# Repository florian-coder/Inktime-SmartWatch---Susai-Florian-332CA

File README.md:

# InkTime v6 — E-Paper Smartwatch

## Overview

InkTime is an e-paper smartwatch built around the **nRF52840** microcontroller, featuring a 1.54" e-paper display, Bluetooth Low Energy connectivity, haptic feedback, and an accelerometer. The watch is powered by a 250mAh LiPo battery managed by a dedicated charger IC with USB-C charging support.

---

## Block Diagram

```
                                    ┌──────────────┐
                                    │   USB-C (J4)  │
                                    │ KH-TYPE-C-16P │
                                    └──────┬───────┘
                                           │ VBUS, D+, D-
                                    ┌──────▼───────┐
                                    │  ESD Protect  │
                                    │ USBLC6-2SC6Y  │
                                    │     (D4)      │
                                    └──────┬───────┘
                              D+,D- │      │ VBUS
                         ┌──────────┘      │
                         │          ┌──────▼───────┐
                         │          │ LiPo Charger  │
                         │          │  BQ25180 (IC3)│
                         │          └──────┬───────┘
                         │                 │ VBAT
                         │          ┌──────▼───────┐
                         │          │  DC/DC Conv   │
                         │          │ RT6160 (IC2)  │
                         │          └──────┬───────┘
                         │                 │ 3V3 (VREG)
                         │                 │
                  ┌──────▼─────────────────▼──────────┐
                  │                                    │
                  │         nRF52840 (U$1)             │
                  │                                    │
                  │  SPI: MOSI, SCK, CS, DC, RST, BUSY │
                  │  I2C: SDA, SCL                     │
                  │  GPIO: Buttons, Haptic EN           │
                  │  USB: D+, D-                       │
                  │  RF: ANT                           │
                  │  SWD: SWDIO, SWDCLK                │
                  │                                    │
                  └─┬──────┬──────┬──────┬──────┬──┬──┘
                    │      │      │      │      │  │
              ┌─────▼──┐ ┌─▼────┐│ ┌────▼─┐ ┌──▼┐ │
              │E-Paper ││ │ IMU  ││ │Haptic│ │ANT│ │
              │Display ││ │BMA423││ │Driver│ │   │ │
              │  (J1)  ││ │(IC1) ││ │DRV   │ │2.4│ │
              │503480  ││ │      ││ │2605  │ │GHz│ │
              └────────┘│ └──────┘│ │(IC4) │ └───┘ │
                        │        │ └──────┘        │
                   ┌────▼───┐ ┌──▼─────┐    ┌─────▼──┐
                   │  Fuel   │ │Buttons │    │  SWD   │
                   │ Gauge   │ │SW1-SW3 │    │  J2    │
                   │MAX17048 │ │        │    │TC2030  │
                   │  (U1)   │ │        │    │        │
                   └─────────┘ └────────┘    └────────┘
```

### Communication Interfaces

| Interface | Components | Signals |
|-----------|-----------|---------|
| SPI | E-Paper Display (J1) | MOSI, SCK, EPD_CS, EPD_DC, EPD_RST, EPD_BUSY |
| I2C | IC1 (IMU), IC2 (DC/DC), IC3 (Charger), IC4 (Haptic), U1 (Fuel Gauge) | SDA, SCL (pull-ups R13=3K3, R14=3K3) |
| USB 2.0 | USB-C Connector (J4) via ESD (D4) | D+, D- (differential 90Ω) |
| SWD | Tag-Connect (J2) | SWDIO, SWDCLK, SWO, RESET |
| GPIO | Buttons (SW1-SW3), Haptic enable, Interrupts | Various P0.xx/P1.xx pins |
| RF | Chip Antenna (ANT1) via matching network | 50Ω controlled impedance trace |

---

## Bill of Materials (BOM)

### Main ICs

| Ref | Component | Package | Value/Description | Qty | Datasheet | Source |
|-----|-----------|---------|-------------------|-----|-----------|--------|
| U$1 | nRF52840-QIAA | QFN-73 7x7mm | BLE SoC, ARM Cortex-M4F, 1MB Flash | 1 | [Datasheet](https://infocenter.nordicsemi.com/pdf/nRF52840_PS_v1.1.pdf) | [JLCPCB](https://jlcpcb.com/partdetail/Nordic_Semiconductor-nRF52840_QIAA_R7/C190794) |
| IC1 | BMA423 | LGA-12 2x2mm | 3-axis accelerometer (IMU) | 1 | [Datasheet](https://www.bosch-sensortec.com/products/motion-sensors/accelerometers/bma423/) | [TME](https://www.tme.eu/en/details/bma423/accelerometers/) |
| IC2 | RT6160AWSC | WLCSP-20 | DC/DC Buck-Boost converter | 1 | [Datasheet](https://www.richtek.com/assets/product_file/RT6160A/DS6160A-05.pdf) | [JLCPCB](https://jlcpcb.com/partdetail/Richtek-RT6160AWSC/C2828074) |
| IC3 | BQ25180YBGR | DSBGA-15 | LiPo Battery Charger | 1 | [Datasheet](https://www.ti.com/lit/ds/symlink/bq25180.pdf) | [JLCPCB](https://jlcpcb.com/partdetail/Texas_Instruments-BQ25180YBGR/C2682568) |
| IC4 | DRV2605YZFR | DSBGA-12 | Haptic Driver | 1 | [Datasheet](https://www.ti.com/lit/ds/symlink/drv2605.pdf) | [JLCPCB](https://jlcpcb.com/partdetail/Texas_Instruments-DRV2605YZFR/C527428) |
| U1 | MAX17048G+T10 | TDFN-8 | Fuel Gauge (battery level) | 1 | [Datasheet](https://datasheets.maximintegrated.com/en/ds/MAX17048-MAX17049.pdf) | [JLCPCB](https://jlcpcb.com/partdetail/Analog_Devices-MAX17048G_T10/C2682568) |

### Connectors & Electromechanical

| Ref | Component | Description | Qty | Source |
|-----|-----------|-------------|-----|--------|
| J1 | 503480-2400 (Molex) | 24-pin FPC connector for e-paper | 1 | [TME](https://www.tme.eu/en/details/503480-2400/ffc-fpc-connectors/) |
| J2 | TC2030-IDC | 6-pin Tag-Connect SWD programmer | 1 | [TME](https://www.tme.eu/en/details/tc2030-idc/) |
| J4 | KH-TYPE-C-16P | USB Type-C 16-pin connector | 1 | [JLCPCB](https://jlcpcb.com/partdetail/Kinghelm-KH_TYPE_C_16P/C2765186) |
| SW1-SW3 | EVP-AKE31A (Panasonic) | Tactile switch 3x2.5mm | 3 | [TME](https://www.tme.eu/en/details/evp-ake31a/micro-switches/) |
| ANT1 | 2450AT18B100E | 2.4GHz chip antenna | 1 | [TME](https://www.tme.eu/en/details/2450at18b100e/) |

### Passive Components — Crystals

| Ref | Value | Description | Qty |
|-----|-------|-------------|-----|
| X1 | 32MHz | Main crystal for nRF52840 | 1 |
| X2 | 32.768kHz | RTC crystal for low-power timekeeping | 1 |

### Passive Components — Inductors

| Ref | Value | Description | Qty |
|-----|-------|-------------|-----|
| L1 | 47µH (FTC252012SR47MBCA) | DC/DC main inductor | 1 |
| L3 | 3.9nH | RF matching network | 1 |
| L5 | 68µH | E-paper drive inductor | 1 |
| U$2, U$4, U$5 | 10µH | MCU inductors (DCC/DCCH) | 3 |

### Passive Components — Capacitors

| Ref | Value | Description | Qty |
|-----|-------|-------------|-----|
| C1, C17, C18 | 12pF | Crystal load capacitors | 3 |
| C3, C4 | 1pF | RF matching | 2 |
| C5, C6, C7, C19, C22 | 100nF | Bypass/decoupling MCU & IMU | 5 |
| C8 | 100pF | DEC4 bypass | 1 |
| C9 | 820pF | RF matching | 1 |
| C11, C14, C20, C21 | 4.7µF | Bulk decoupling MCU | 4 |
| C15 | 1.0µF | VDDH capacitor | 1 |
| C16 | 47nF | DEC4 capacitor | 1 |
| C23, C2, C30 | 0.1µF | Bypass DC/DC, Haptic, USB | 3 |
| C24 | 10µF | DC/DC output | 1 |
| C25, C33 | 22µF | DC/DC input/output | 2 |
| C27, C28, C29 | 1µF | Button debounce | 3 |
| C31 | 4.7µF | USB bulk capacitor | 1 |
| C32-C44 | 1µF/50V | E-paper drive capacitors | 9 |
| C37, C38, C4 | 1µF | Charger & haptic bypass | 3 |
| C39 | 10µF | Charger output | 1 |
| C1-EP-DR | 4.7µF/25V | E-paper drive main cap | 1 |
| C10, C12, C13 | N.C. | Not connected (reserved) | 3 |

### Passive Components — Resistors

| Ref | Value | Description | Qty |
|-----|-------|-------------|-----|
| R1, R2, R3 | 0Ω | IMU configuration jumpers | 3 |
| R6, R7, R8 | 10K | Button pull-up resistors | 3 |
| R9, R12, R15 | 10K | Charger TS, E-paper config | 3 |
| R10 | 0.47Ω | E-paper current sense | 1 |
| R11 | 2.2Ω | E-paper type select | 1 |
| R13, R14 | 3K3 | I2C pull-ups (SCL, SDA) | 2 |
| R16 | 5K1 | USB-C CC resistor | 1 |

### Semiconductors

| Ref | Component | Description | Qty |
|-----|-----------|-------------|-----|
| D1, D2, D3 | MBR0530 | Schottky diodes (e-paper drive) | 3 |
| D4 | USBLC6-2SC6Y | USB ESD protection | 1 |
| Q1 | SI1308EDL-T1-GE3 | N-MOSFET (e-paper drive) | 1 |
| U$3 | DMG2305UX-7 | P-MOSFET (e-paper drive) | 1 |

### Off-Board Components

| Component | Model | Dimensions | Description |
|-----------|-------|------------|-------------|
| Battery | LP502030 (Akyga AKY0106) | 30×20×5mm | 3.7V 250mAh LiPo |
| Display | WSH-12561 (Waveshare) | 31.8×37.32×1.05mm | 1.54" e-paper 200x200px |
| Shaker | FIT0774 (DFRobot) | Ø10×2.7mm | Mini vibration motor |

---

## Pin Assignment — nRF52840 (U$1)

### SPI — E-Paper Display

| nRF52840 Pin | Signal | Direction | Connected To | Purpose |
|-------------|--------|-----------|-------------|---------|
| P0.13 | MOSI | Output | J1 pin 14 | SPI data to display |
| P0.14 | SCK | Output | J1 pin 13 | SPI clock |
| P1.01 | EPD_CS | Output | J1 pin 12 | Chip select (active low) |
| P1.02 | EPD_DC | Output | J1 pin 11 | Data/Command select |
| P0.15 | EPD_RST | Output | J1 pin 10 | Display reset |
| P0.16 | EPD_BUSY | Input | J1 pin 9 | Display busy status |

**Why these pins:** P0.13 and P0.14 are the default SPI MOSI/SCK pins on the nRF52840. The control signals (CS, DC, RST, BUSY) use nearby GPIO pins on the P1.0x port for clean routing to the FPC connector on the left side of the board.

### I2C Bus — Shared (SDA/SCL)

| nRF52840 Pin | Signal | Connected To | Pull-up |
|-------------|--------|-------------|---------|
| P0.26 | SDA | IC1, IC2, IC3, IC4, U1 | R14 = 3K3 to 3V3 |
| P0.27 | SCL | IC1, IC2, IC3, IC4, U1 | R13 = 3K3 to 3V3 |

**Why these pins:** P0.26/P0.27 are the default TWI (I2C) pins. All five I2C devices share the same bus, each with a unique address. The 3K3 pull-up value is chosen for the bus capacitance with 5 devices at 400kHz.

**I2C Device Addresses:**
| Device | Address | Function |
|--------|---------|----------|
| IC1 (BMA423) | 0x18 or 0x19 | Accelerometer (configured via R1-R3) |
| IC2 (RT6160) | 0x75 | DC/DC voltage setting |
| IC3 (BQ25180) | 0x6A | Battery charger configuration |
| IC4 (DRV2605) | 0x5A | Haptic driver control |
| U1 (MAX17048) | 0x36 | Battery fuel gauge |

### USB 2.0

| nRF52840 Pin | Signal | Connected To |
|-------------|--------|-------------|
| D- (P$AD4) | USB D- | J4 via D4 (ESD) |
| D+ (P$AD6) | USB D+ | J4 via D4 (ESD) |
| VBUS (P$AD2) | USB VBUS | J4 VBUS pin |

**Why:** Dedicated USB pins on the nRF52840, directly mapped in hardware. D+/D- routed as 90Ω differential pair with matched lengths.

### SWD Programming

| nRF52840 Pin | Signal | Connected To |
|-------------|--------|-------------|
| SWDIO (P$AC24) | SWDIO | J2 pin 2 |
| SWDCLK (P$AA24) | SWDCLK | J2 pin 4 |
| P0.18/RESET | RESET | J2 pin 6 |
| P0.09 | SWO | J2 pin 3 (via TP_SWO) |

**Why:** SWDIO and SWDCLK are fixed SWD pins. P0.09 is used for SWO (Serial Wire Output) for debug tracing. RESET is the dedicated reset pin.

### Interrupt Lines

| nRF52840 Pin | Signal | Source | Purpose |
|-------------|--------|--------|---------|
| P0.04 | IMU_INT1 | IC1 pin 5 | Accelerometer interrupt 1 (step detection, tap) |
| P0.05 | IMU_INT2 | IC1 pin 6 | Accelerometer interrupt 2 (data ready) |
| P1.09 | PMIC_INT | IC3 pin A1 | Charger status interrupt |
| P0.25 | HAPTIC_EN | IC4 pin B1 | Haptic driver enable/trigger |
| P1.01 | ALERT | U1 pin 5 | Battery low alert from fuel gauge |

**Why:** Interrupt pins are chosen on the P0.04-P0.05 range which support GPIOTE (GPIO Tasks and Events) for low-latency wake-up from sleep mode. PMIC_INT on P1.09 for charger monitoring.

### Buttons

| nRF52840 Pin | Signal | Connected To | Pull-up | Debounce |
|-------------|--------|-------------|---------|----------|
| P0.28 | BTN_UP | SW1 pin 2 | R8 = 10K | C27 = 1µF |
| P0.29 | BTN_ENTER | SW2 pin 2 | R7 = 10K | C28 = 1µF |
| P0.30 | BTN_DOWN | SW3 pin 2 | R6 = 10K | C29 = 1µF |

**Why:** P0.28-P0.30 are analog-capable pins (AIN4-AIN6) but used here as digital GPIO with internal pull-up supplemented by external 10K pull-ups. The 1µF debounce capacitors with 10K resistors give a ~10ms time constant, effective for mechanical button debounce. Buttons are active-low (pressed = GND).

### Power Pins

| nRF52840 Pin | Signal | Description |
|-------------|--------|-------------|
| VDD (multiple) | 3V3 | Main 3.3V supply from DC/DC |
| VDDH | VREG | Higher voltage input (from battery via DC/DC) |
| VBUS | VBUS | USB 5V input detection |
| DCC/DCCH | Internal | Internal DC/DC converter pins (U$2, U$4, U$5 inductors) |
| DEC1-DEC6 | Bypass | Decoupling pins (C5, C6, C7, C8, C16, C22) |
| VSS, VSS_PA | GND | Ground connections |

### RF

| nRF52840 Pin | Signal | Connected To |
|-------------|--------|-------------|
| ANT (P$H23) | RF output | ANT1 via matching network (L3→C3→C9) |
| VSS_PA (P$F23) | RF ground | GND plane |

**Why:** The ANT pin is the dedicated RF output. The matching network (L3=3.9nH, C3=1pF, C9=820pF) transforms the impedance to 50Ω for the chip antenna. A keep-out zone with no copper on any layer is maintained under and around ANT1.

---

## Hardware Detailed Description

### Power Architecture

The power system follows a three-stage architecture:

**Stage 1 — USB Input & Charging:** USB-C connector (J4) provides 5V VBUS. The USBLC6-2SC6Y (D4) provides ESD protection on D+/D- and VBUS lines. R16 (5K1) on CC1 identifies the device as a USB sink. VBUS feeds into IC3 (BQ25180) which charges the LiPo battery with configurable current (up to 1A) and provides system power during charging.

**Stage 2 — Battery Management:** The BQ25180 (IC3) manages charging with features including power path management (system runs from VBUS when connected, seamlessly switches to battery when disconnected), battery temperature monitoring via TS/MR pin (R9=10K), and I2C configuration for charge current and voltage. The MAX17048 fuel gauge (U1) monitors battery voltage and state-of-charge using a ModelGauge algorithm — no sense resistor needed, it measures the battery directly via CELL pin.

**Stage 3 — Voltage Regulation:** The RT6160 (IC2) buck-boost converter takes VBAT (3.0V-4.2V) and produces a stable 3V3 output (VREG). Buck-boost topology ensures operation even when battery voltage drops below 3.3V. The switching frequency is set internally, with the external inductor L1 (47µH) chosen for low DCR and sufficient current handling. Input capacitors (C33=22µF, C23=0.1µF) and output capacitors (C24=10µF, C25=22µF) are sized per the datasheet recommendations. The DC/DC has I2C interface for dynamic voltage adjustment if needed.

### Power Consumption Estimate

| State | Current | Duration | Notes |
|-------|---------|----------|-------|
| Deep sleep (RTC only) | ~1.5µA | 99% of time | nRF52840 System OFF + RTC |
| Display refresh | ~15mA | 2s per refresh | E-paper full update |
| BLE advertising | ~5mA | 1-2ms per event | Every 1-2 seconds |
| BLE connected | ~8mA | During data transfer | Intermittent |
| Haptic vibration | ~50mA | 100-500ms per event | Motor on |
| Active processing | ~3mA | Brief periods | CPU running at 64MHz |

**Estimated battery life:** With a 250mAh battery, primarily in deep sleep with occasional BLE activity and 1 display refresh per minute, the estimated battery life is approximately 5-10 days.

### E-Paper Display System

The 1.54" e-paper display (Waveshare WSH-12561, 200x200 pixels) connects via a 24-pin FPC connector (J1, Molex 503480-2400). The display uses SPI for data transfer and requires a complex drive circuit for the e-ink panel voltages.

**E-Paper Drive Circuit:** The display requires multiple voltage rails (PREVGH ~+15V, PREVGL ~-15V, VGH, VGL) generated by a boost/inverter circuit built from:
- U$3 (DMG2305UX-7, P-MOSFET) and Q1 (SI1308EDL, N-MOSFET) — switching elements
- L5 (68µH) — energy storage inductor
- D1, D2, D3 (MBR0530) — Schottky rectifier diodes
- C32-C44 (1µF/50V × 9) — high-voltage filter capacitors
- R10 (0.47Ω) — current sense resistor
- R11 (2.2Ω) — display type select

The drive circuit generates the required voltages from the 3V3 rail through a charge pump / boost converter topology controlled by the nRF52840 GPIO pins.

### IMU (Accelerometer)

The BMA423 (IC1) is a low-power 3-axis accelerometer featuring built-in step counter, tap detection, and activity recognition. It communicates via I2C at up to 400kHz. Configuration jumpers R1, R2, R3 (0Ω) set the SDO address bit, SDX/SCX mode, and CSB for I2C mode selection. The bypass capacitor C19 (100nF) is placed within 1mm of the VDD pin.

**Placement note:** IC1 is placed away from IC4 (haptic driver) to avoid vibration interference with the accelerometer readings.

### Haptic Feedback

The DRV2605 (IC4) is a haptic driver that drives the FIT0774 coin vibration motor (10mm × 2.7mm). It supports both ERM (Eccentric Rotating Mass) and LRA (Linear Resonant Actuator) motor types with a built-in library of 123 haptic effects. The nRF52840 triggers effects via I2C commands or the HAPTIC_EN GPIO pin. Bypass capacitors C2 (0.1µF) and C4 (1µF) provide local decoupling.

### Bluetooth Low Energy

The nRF52840 integrates a 2.4GHz radio with BLE 5.0 support. The RF signal is routed from the ANT pin through a pi-network matching circuit (L3=3.9nH, C3=1pF, C9=820pF) to the 2450AT18B100E chip antenna (ANT1). The matching network values are per the nRF52840 reference design for 50Ω impedance.

**RF Layout Rules Applied:**
- No copper (GND or signal) on any layer under the antenna
- 2mm minimum keep-out zone around ANT1
- 50Ω controlled impedance trace from matching network to antenna
- Matching components placed in series on the RF trace, as close to ANT pin as possible

---

## PCB Design Details

### Board Specifications

| Parameter | Value |
|-----------|-------|
| Dimensions | 46 × 35 mm (watch form factor) |
| Thickness | 1.0 mm |
| Layers | 4 (Top, GND, Power, Bottom) |
| Copper weight | 1oz (35µm) |
| Min trace width | 5mil (0.127mm) |
| Min clearance | 5mil (0.127mm) |
| Min drill | 0.3mm |
| Copper to edge | 0.2mm |
| Fabricator | JLCPCB |

### Layer Stack-up

| Layer | Name | Type | Content |
|-------|------|------|---------|
| 1 | Top | Signal | Components + signal routing + GND pour |
| 2 | GND | Plane | Dedicated GND plane (polygon pour) |
| 63 | Power | Signal | Additional routing layer |
| 64 | Bottom | Signal | Signal routing + GND pour |

### Component Placement Strategy

All components are placed on the **TOP layer** as required. The placement follows functional grouping:

- **Center:** nRF52840 (U$1) with bypass capacitors and crystals immediately adjacent
- **Top-center:** USB-C (J4, fixed) with ESD protection (D4) and charger (IC3) nearby for short VBUS trace
- **Top-right corner:** Antenna (ANT1) with RF keep-out zone — no copper on any layer
- **Left side:** E-paper connector (J1, fixed) with entire drive circuit (MOSFETs, diodes, inductor, capacitors)
- **Bottom-left:** DC/DC converter (IC2) with inductor L1 adjacent for short switching loop
- **Center-bottom:** IMU (IC1) — away from haptic driver
- **Right side:** Haptic driver (IC4) and fuel gauge (U1) — away from IMU
- **Bottom edge:** Buttons (SW1-SW3, fixed) with pull-up resistors and debounce capacitors adjacent
- **Right edge:** SWD connector (J2) for programming access

### Fixed Components (from enclosure constraints)

The following components are pre-placed in the .fbrd file and aligned with the physical enclosure:
- **J1** (503480-2400) — E-paper FPC connector, left notch
- **J4** (KH-TYPE-C-16P) — USB-C connector, top edge
- **SW1, SW2, SW3** (EVP-AKE31A) — Buttons, bottom edge, aligned with enclosure button openings

### Routing Notes

- **Power traces** (VBUS, VBAT, 3V3, LX1, LX2): ≥0.3mm width
- **Signal traces** (SPI, I2C, GPIO): 0.15-0.2mm width
- **USB D+/D-**: Differential pair, 90Ω impedance, matched lengths
- **RF trace**: 50Ω controlled impedance, TOP layer only, no vias
- **GND plane**: Continuous on layer 2, polygon pour on Top and Bottom
- **Via stitching**: GND vias around board perimeter every 4-5mm
- **U$1 thermal pad**: 9-12 GND vias under exposed pad

---

## Design Decisions & Known Issues

### Design Log

1. **Started with 2-layer stackup** — initial routing achieved ~70% completion with autorouter. The remaining 30% of airwires could not be resolved due to board density (46×35mm with ~100 components).

2. **Migrated to 4-layer stackup** — added dedicated GND plane (layer 2) and additional routing layer (layer 63). This improved routing completion significantly.

3. **Autorouter strategy** — used Fusion Electronics built-in autorouter with Effort=High, TopRouter variant. Multiple passes were run to maximize routing completion. Remaining unrouted signals were attempted manually.

4. **DRC violations approved** — 132 warnings were approved due to board density constraints:
   - 42 Overlap warnings (via-via, via-smd on GND plane — expected behavior)
   - 38 Copper Clearance warnings (traces in dense areas slightly below 5mil clearance)
   - 36 Board Outline Clearance warnings (components near board edge)
   - 12 Component Exclude Clearance (tight component spacing)
   - 4 Drill Clearance warnings (vias near board outline)

5. **Silkscreen** — contains only component reference designators (NamesTop layer). Value labels were hidden as they contained library metadata strings instead of clean values.

6. **Battery connection** — per requirements, the battery connects directly to test pads TP_VBAT and TP_BAT_GND (no JST connector on board).

### Known Limitations

- Board density at 46×35mm on 4 layers is at the practical limit for this component count
- Some copper clearance violations exist in the dense MCU area — could be resolved with more manual routing optimization
- RF matching network values should be verified with a VNA (Vector Network Analyzer) after fabrication
- E-paper drive circuit component values may need tuning for the specific display panel used

---

## 3D Assembly

The complete device assembly (exploded view) shows the mechanical stack-up:

1. **E-Paper Display** (top) — 32×30×1.05mm, positioned 1.5mm above PCB surface
2. **PCB** (middle) — 46×35×1.0mm, 4-layer board with all components on top
3. **Battery** (bottom) — 30×20×5mm, centered under PCB, 0.5mm clearance
4. **Shaker Motor** (bottom) — Ø10×2.7mm, positioned under IC4 (haptic driver area), 0.5mm clearance

Total stack height: ~1.05 + 1.5 + 1.0 + 0.5 + 5.0 = **~9.05mm** (without enclosure)

---

## File Structure

```
InkTime/
├── Hardware/
│   ├── InkTime-schematic.fsch          # Fusion Electronics schematic
│   ├── InkTime-pcb-v1.fbrd            # Fusion Electronics board
│   └── Schematic.pdf                   # Schematic print-out
├── Manufacturing/
│   ├── gerbers.zip                     # Gerber + drill files for fabrication
│   ├── InkTime-pcb-v1.bom             # Bill of Materials
│   └── PnP_InkTime-pcb-v1_front.cpl   # Pick and Place file
├── Mechanical/
│   ├── InkTime-exploded.step           # 3D STEP exploded view
│   └── InkTime-pcb-v1-3d.f3z          # Fusion 360 3D assembly
├── Images/
│   ├── pcb-top-3d.png                  # 3D render - top view
│   ├── pcb-bottom-3d.png              # 3D render - bottom view
│   ├── pcb-isometric-3d.png           # 3D render - isometric
│   ├── assembly-exploded.png          # Exploded view render
│   └── assembly-side.png             # Side view showing stack-up
├── LICENSE
└── README.md
```

---

## References

- [nRF52840 Product Specification](https://infocenter.nordicsemi.com/pdf/nRF52840_PS_v1.1.pdf)
- [nRF52840 Reference Circuit Layout](https://infocenter.nordicsemi.com/topic/com.nordic.infocenter.nrf52840/intf_radio_circuit.html)
- [BQ25180 Datasheet](https://www.ti.com/lit/ds/symlink/bq25180.pdf)
- [RT6160A Datasheet](https://www.richtek.com/assets/product_file/RT6160A/DS6160A-05.pdf)
- [BMA423 Datasheet](https://www.bosch-sensortec.com/products/motion-sensors/accelerometers/bma423/)
- [DRV2605 Datasheet](https://www.ti.com/lit/ds/symlink/drv2605.pdf)
- [MAX17048 Datasheet](https://datasheets.maximintegrated.com/en/ds/MAX17048-MAX17049.pdf)
- [Waveshare 1.54" E-Paper Specification](https://www.waveshare.com/w/upload/7/77/1.54inch_e-Paper_Datasheet.pdf)
- [PCB Silkscreen Guidelines (Altium)](https://resources.altium.com/p/your-guide-pcb-silkscreen)
- [PCB Silkscreen Guidelines (Cadence)](https://resources.pcb.cadence.com/blog/2022-essential-pcb-silkscreen-guidelines-for-layout)

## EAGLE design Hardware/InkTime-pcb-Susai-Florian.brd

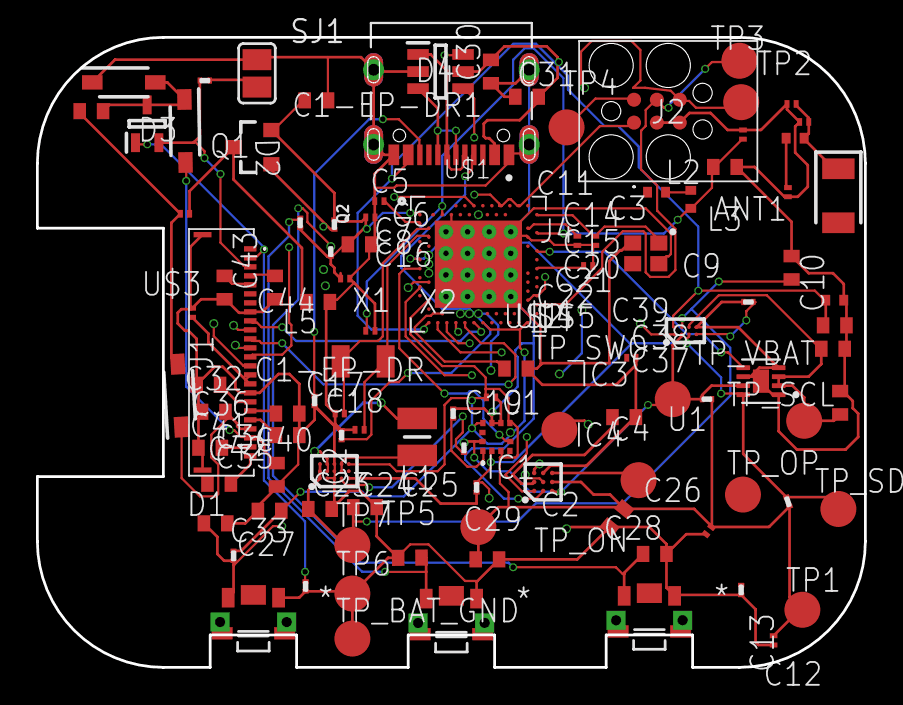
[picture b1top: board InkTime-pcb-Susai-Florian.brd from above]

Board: 4 copper layers, 46.0 x 35.0 mm, 105 parts (0 on the bottom side), 69 nets.

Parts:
ANT1: 2450AT18B100E_2450AT18B100E; 2450AT18B100E_ANTC3216X140N
C1, C3: 1pF; NORDIC_NRF_3_RESC0201_L
C1-EP-DR, C24, C39: 10uF; ESP32_C6_LIBRARY_1_ESP32_WROVER_EAGLE-LTSPICE_C0402
C1-EP-DR1: 4.7uF/25V; ESP32_C6_LIBRARY_1_ESP32_WROVER_EAGLE-LTSPICE_C0402
C2, C23, C26, C31: 0.1uF; ESP32_C6_LIBRARY_1_ESP32_WROVER_EAGLE-LTSPICE_C0402
C4, C27, C28, C29, C37, C38: 1uF; ESP32_C6_LIBRARY_1_ESP32_WROVER_EAGLE-LTSPICE_C0402
C5, C7, C8, C12, C19: 100nF; NORDIC_NRF_3_RESC0201_L
C6, C14, C20: 4.7µF; ESP32_C6_LIBRARY_1_ESP32_WROVER_EAGLE-LTSPICE_C0402
C9: 820pF; NORDIC_NRF_3_RESC0201_L
C10, C13, C22: N.C.; NORDIC_NRF_3_RESC0201_L
C11: 100pF; NORDIC_NRF_3_RESC0201_L
C15: 1.0µF; ESP32_C6_LIBRARY_1_ESP32_WROVER_EAGLE-LTSPICE_C0402
C16: 47nF; NORDIC_NRF_3_RESC0201_L
C17, C18: 12pF; NORDIC_NRF_3_RESC0201_L
C21: 4.7µF; NORDIC_NRF_3_RESC0402_L
C25, C33: 22uF; ESP32_C6_LIBRARY_1_ESP32_WROVER_EAGLE-LTSPICE_C0402
C30: 4.7uF; ESP32_C6_LIBRARY_1_ESP32_WROVER_EAGLE-LTSPICE_C0402
C32, C34, C35, C36, C40, C41, C42, C43, C44: 1uF/50V; ESP32_C6_LIBRARY_1_ESP32_WROVER_EAGLE-LTSPICE_C0402
D1, D2, D3: ESP32_C6_LIBRARY_5_MBR0530; ESP32_C6_LIBRARY_5_SOD3716X135N
D4: ESP32_C6_LIBRARY_3_USBLC6-2SC6Y; ESP32_C6_LIBRARY_3_SOT95P280X145-6N
IC1: BMA423_BMA423
IC2: RT6160AWSC_RT6160AWSC; RT6160AWSC_BGA15C40P3X5_140X230X60
IC3: BQ25180YBGR_BQ25180YBGR; BQ25180YBGR_BGA8C40P2X4_100X155X50
IC4: DRV2605YZFR_DRV2605YZFR; DRV2605YZFR_BGA9C50P3X3_144X144X62
J1: 503480-2400_503480-2400; 503480-2400_5034802400
J2: TC2030-IDC_TC2030-IDC; TC2030-IDC_TC2030IDC
J4: KH-TYPE-C-16P_KH-TYPE-C-16P; KH-TYPE-C-16P_KINGHELM_KH-TYPE-C-16P
L1: MLP2016SR47MT0S1_FTC252012SR47MBCA; MLP2016SR47MT0S1_INDC2016X100N
L2, L3: 10µH; NORDIC_NRF_2_RESC0402_L
L5: 68uH; NORDIC_NRF_2_RESC0201_L
Q1: ESP32_C6_LIBRARY_6_SI1308EDL-T1-GE3; ESP32_C6_LIBRARY_6_SOT65P210X110-3N
Q2: 20V/4.2A/52mΩ/1.4W; ESP32_C6_LIBRARY_4_ESP32_C6_LIBRARY_4_ESP32_C6_LIBRARY_4_ES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
R1, R2, R3: 0; CPF0201D7K68C1_0201
R4, R5: 3K3; CPF0201D7K68C1_0201
R6: 0.47; CPF0201D7K68C1_0201
R7: 2.2; CPF0201D7K68C1_0201
R8, R9, R10, R11, R12, R13, R14, R16: 10K; CPF0201D7K68C1_0201
SJ1: 0; ESP32_C6_LIBRARY_7_JUMPER_SJ
SW1, SW2, SW3: 2025-10-22_07-23-44_LIBRARY_EVP-AKE31ASW_EVP-AKE3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; 2025-10-22_07-23-44_LIBRARY_SW_EVP-AKE31A_PAN
TP1, TP2, TP3, TP4, TP5, TP6, TP7: HECTOR_WATCH_1_TPTP20R; HECTOR_WATCH_1_TP20R
TP_BAT_GND: HECTOR_WATCH_1_TPTP20R; HECTOR_WATCH_1_TP20R
TP_ON: HECTOR_WATCH_1_TPTP20R; HECTOR_WATCH_1_TP20R
TP_OP: HECTOR_WATCH_1_TPTP20R; HECTOR_WATCH_1_TP20R
TP_SCL: HECTOR_WATCH_1_TPTP20R; HECTOR_WATCH_1_TP20R
TP_SDA: HECTOR_WATCH_1_TPTP20R; HECTOR_WATCH_1_TP20R
TP_SWO: HECTOR_WATCH_1_TPTP20R; HECTOR_WATCH_1_TP20R
TP_VBAT: HECTOR_WATCH_1_TPTP20R; HECTOR_WATCH_1_TP20R
U1: ESP32_C6_LIBRARY_MAX17048G+T10; ESP32_C6_LIBRARY_SON50P200X200X80-9N
U$1: NORDIC_NRF_4_NRF52840_QF; NORDIC_NRF_4_AQFN50P700X700X85_HS-74N
U$2: 3.9nH; NORDIC_NRF_2_RESC0402_L
U$3: 1uF/50V; NORDIC_NRF_3_RESC0201_L
U$4, U$5: 12pF; NORDIC_NRF_3_RESC0201_L
X1: 32MHz; NORDIC_NRF_BT-XTAL_2016_N
X2: 32.768kHz; NORDIC_NRF_1_XTAL_3215_N

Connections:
3V3: C2.1, C12.1, C13.1, C19.1, C25.1, C33.1, IC1.3, IC1.7, IC1.10, IC2.E3, IC4.C2, R4.1, R5.1, R10.2, TP1.TP, TP5.TP, U$1.P$AD14, U$1.P$AD23, U$1.P$Y2
ALERT: U1.5, U$1.P$J24
D+: D4.4, U$1.P$AD6
D-: D4.6, U$1.P$AD4
DEC3: C11.1, U$1.P$D23
DEC4_6: C10.1, C15.1, C16.1, L3.2, U$1.P$B5, U$1.P$E24
DN: D4.1, J4.A7, J4.B7
DP: D4.3, J4.A6, J4.B6
EPD: J1.15, J1.16, U$3.2
EPD_3V3: C1-EP-DR.1, L5.1, Q2.3
EPD_BUSY: J1.9, U$1.P$AD12
EPD_CS: J1.12, U$1.P$K2
EPD_DC: J1.11, U$1.P$AD10
EPD_RST: J1.10, U$1.P$AC11
GDR: J1.2, Q1.1, R8.2
GND: C1-EP-DR.2, C2.2, C4.2, C5.2, C6.2, C7.2, C8.2, C9.2, C11.2, C12.2, C13.2, C14.2, C16.2, C17.1, C18.1, C19.2, C20.2, C23.2, C24.2, C25.2, C27.2, C28.2, C29.2, C30.1, C31.1, C32.1, C33.2, C34.1, C35.1, C36.1, C40.1, C41.1, C43.1, C44.1, D3.1, D4.2, IC1.8, IC1.9, IC2.B1, IC2.C1, IC2.C2, IC2.C3, IC4.B1, IC4.B3, J1.8, J1.17, J1.MP1, J1.MP2, J4.A1_B12, J4.A12_B1, J4.SH1, J4.SH2, J4.SH3, J4.SH4, R3.1, R7.1, R8.1, R13.1, R14.2, SJ1.1, SW1.1, SW2.1, SW3.1, TP6.TP, TP_BAT_GND.TP, U$1.P$74, U$1.P$75, U$1.P$76, U$1.P$77, U$1.P$78, U$1.P$79, U$1.P$80, U$1.P$81, U$1.P$82, U$1.P$83, U$1.P$84, U$1.P$85, U$1.P$86, U$1.P$87, U$1.P$88, U$1.P$89, U$1.P$90, U$1.P$B7, U$1.P$F23, U$3.1, U$4.2, U$5.2, X1.2, X1.4
GND3: IC1.1, R3.2
HAPTIC_EN: IC4.A1, U$1.P$U1
IMU_INT1: IC1.5, U$1.P$N1
IMU_INT2: IC1.6, U$1.P$P2
LX1: IC2.B2, IC2.B3, L1.1
LX2: IC2.D2, IC2.D3, L1.2
MOSI: J1.14, U$1.P$B13
unnamed: C5.1, U$1.P$C1
unnamed: C20.1, U$1.P$AC5
unnamed: ANT1.1, C1.1, C22.1, U$2.2
unnamed: C3.1, U$2.1
unnamed: L2.2, L3.1
unnamed: IC2.D1, R2.2
unnamed: C1-EP-DR1.2, D1.2, L5.2
unnamed: IC2.E1, R1.2
unnamed: C1-EP-DR1.1, D2.1, D3.2, Q1.3
unnamed: C9.1, U$1.P$N24
unnamed: IC3.D1, R9.2
unnamed: U$1.P$B24, U$4.1, X1.1
unnamed: R6.1, SJ1.2
unnamed: C4.1, IC4.A2
unnamed: J4.A5, R13.2
unnamed: J4.B5, R14.1
unnamed: C43.2, J1.4
unnamed: C44.2, J1.5
unnamed: C32.2, J1.18
unnamed: C34.2, J1.19
unnamed: C35.2, J1.20
unnamed: C41.2, J1.23
unnamed: C42.2, J1.24
OUT+: IC4.A3, TP_OP.TP
OUT-: IC4.C3, TP_ON.TP
P0.00/XL1: C17.2, U$1.P$D2, X2.1
P0.00/XL2: C18.2, U$1.P$F2, X2.2
P0.13: C27.1, R10.1, SW1.2, U$1.P$AD8
P0.14: C28.1, R11.1, SW2.2, U$1.P$AC9
P1.01: Q2.1, R16.1, U$1.P$W24, U$1.P$Y23
P1.02: C29.1, R12.1, SW3.2
PMIC_INT: IC3.A1, U$1.P$T2
PREVGH: C36.2, D1.1, J1.21
PREVGL: C40.2, D2.2, J1.22
RESE: J1.3, Q1.2, R6.2
RESET: J2.6, TP2.TP, U$1.P$AC13
S$2: C1.2, C3.2, C10.2, C15.2, C21.2, C22.2, C26.2, C37.2, C38.2, C39.2, IC3.D2, J2.3, J2.5, R9.1, U1.1, U1.4, U1.6, U1.9
S$3: C6.1, C7.1, C8.1, C14.1, J2.1, Q2.2, R11.2, R12.2, R16.2, U$1.P$A18, U$1.P$A22, U$1.P$B1
SCK: J1.13, U$1.P$A12
SCL: IC1.12, IC3.B1, IC4.C1, R2.1, R4.2, TP_SCL.TP, U1.7, U$1.P$M2
SDA: IC1.2, IC3.C1, IC4.B2, R1.1, R5.2, TP_SDA.TP, U1.8, U$1.P$L1
SWDCLK: J2.4, TP3.TP, U$1.P$AA24
SWDIO: J2.2, TP4.TP
VBAT: C26.1, C37.1, IC3.C2, TP_VBAT.TP, U1.2, U1.3
VBUS: C21.1, C30.2, C31.2, C38.1, D4.5, IC3.A2, J4.A4_B9, J4.A9_B4, U$1.P$AD2
VREG: C23.1, C24.1, C39.1, IC2.A1, IC2.A2, IC2.A3, IC3.B2, TP7.TP

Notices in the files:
parts and their libraries:
COPYRIGHT: Copyright (C) 2025 Ultra Librarian. All rights reserved.
